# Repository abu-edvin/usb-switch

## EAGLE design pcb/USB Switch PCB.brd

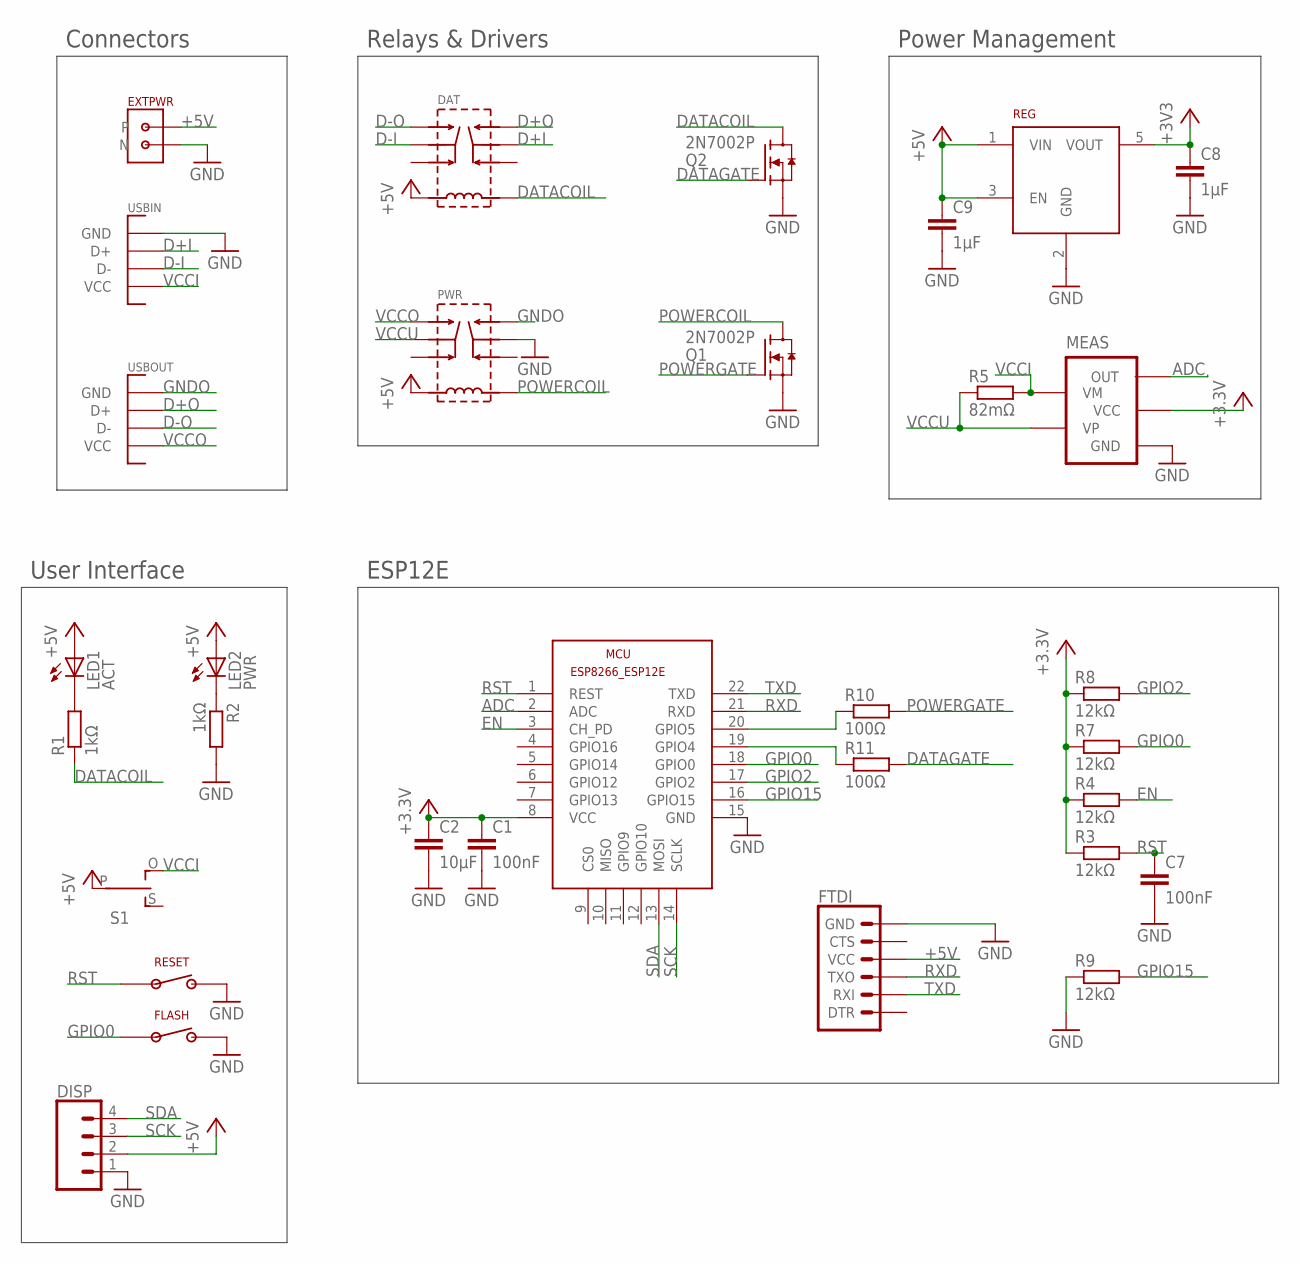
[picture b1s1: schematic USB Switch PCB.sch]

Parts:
C1, C7: 100nF; C0603
C2: 10µF; C0603
C8, C9: 1µF; C0603
DAT: EC2-5NUEC2-5NU; EC2-5NU
DISP: CONN_04; 1X04
EXTPWR: TERMINAL-BLOCK
FLASH: MOMENTARY-SWITCH
FTDI: 6_PIN_SERIAL_TARGET; 1X06
LED1: ACT; CHIPLED_0805
LED2: PWR; CHIPLED_0805
MCU: ESP8266-12EESP8266-ESP12E; ESP8266-ESP12E
MEAS: TCS888; SOT-23-5
PWR: EC2-5NUEC2-5NU; EC2-5NU
Q1, Q2: 2N7002P; SOT23
R1, R2: 1kΩ; R0603
R3, R4, R7, R8, R9: 12kΩ; R0603
R5: 82mΩ; R1206
R10, R11: 100Ω; R0603
REG: MIC5504-3.3YM5SOT23; SOT-23-5
RESET: MOMENTARY-SWITCH
S1: SWITCH
USBIN: USB-B
USBOUT: UE27-USBA

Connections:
+3V3: C8.1, REG.5 (VOUT)
+5V: C1.1, C2.1, C9.1, DAT.1, DISP.2, EXTPWR.P, FTDI.4 (VCC), LED1.A, LED2.A, MCU.8 (VCC), MEAS.5 (VCC), PWR.1, R3.1, R4.1, R7.1, R8.1, REG.1 (VIN), REG.3 (EN), S1.P
ADC: MCU.2 (ADC), MEAS.1 (OUT)
D+I: DAT.9 (C2), USBIN.3 (D+)
D+O: DAT.8 (A2), USBOUT.D+
D-I: DAT.4 (C1), USBIN.2 (D-)
D-O: DAT.5 (A1), USBOUT.D-
DATACOIL: DAT.12 (N), Q2.3 (D), R1.1
DATAGATE: Q2.1 (G), R11.2
EN: MCU.3 (CH_PD), R4.2
GND: C1.2, C2.2, C7.2, C8.2, C9.2, DISP.1, EXTPWR.N, FLASH.P$2, FTDI.6 (GND), MCU.15 (GND), MEAS.2 (GND), PWR.9 (C2), Q1.2 (S), Q2.2 (S), R2.2, R9.1, REG.2 (GND), RESET.P$2, USBIN.4 (GND), USBIN.P$1 (GND), USBIN.P$2 (GND)
GNDO: PWR.8 (A2), USBOUT.GND, USBOUT.P$0 (GND), USBOUT.P$1 (GND)
GPIO0: FLASH.P$1, MCU.18 (GPIO0), R7.2
GPIO2: MCU.17 (GPIO2), R8.2
GPIO15: MCU.16 (GPIO15), R9.2
unnamed: LED1.C, R1.2
unnamed: LED2.C, R2.1
unnamed: MCU.20 (GPIO5), R10.1
unnamed: MCU.19 (GPIO4), R11.1
POWERCOIL: PWR.12 (N), Q1.3 (D)
POWERGATE: Q1.1 (G), R10.2
RST: C7.1, MCU.1 (REST), R3.2, RESET.P$1
RXD: FTDI.3 (TXO), MCU.21 (RXD)
SCK: DISP.3, MCU.14 (SCLK)
SDA: DISP.4, MCU.13 (MOSI)
TXD: FTDI.2 (RXI), MCU.22 (TXD)
VCCI: MEAS.4 (VM), R5.2, S1.O, USBIN.1 (VCC)
VCCO: PWR.5 (A1), USBOUT.VCC
VCCU: MEAS.3 (VP), PWR.4 (C1), R5.1

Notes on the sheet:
Connectors
Relays & Drivers
Power Management
ESP12E
User Interface

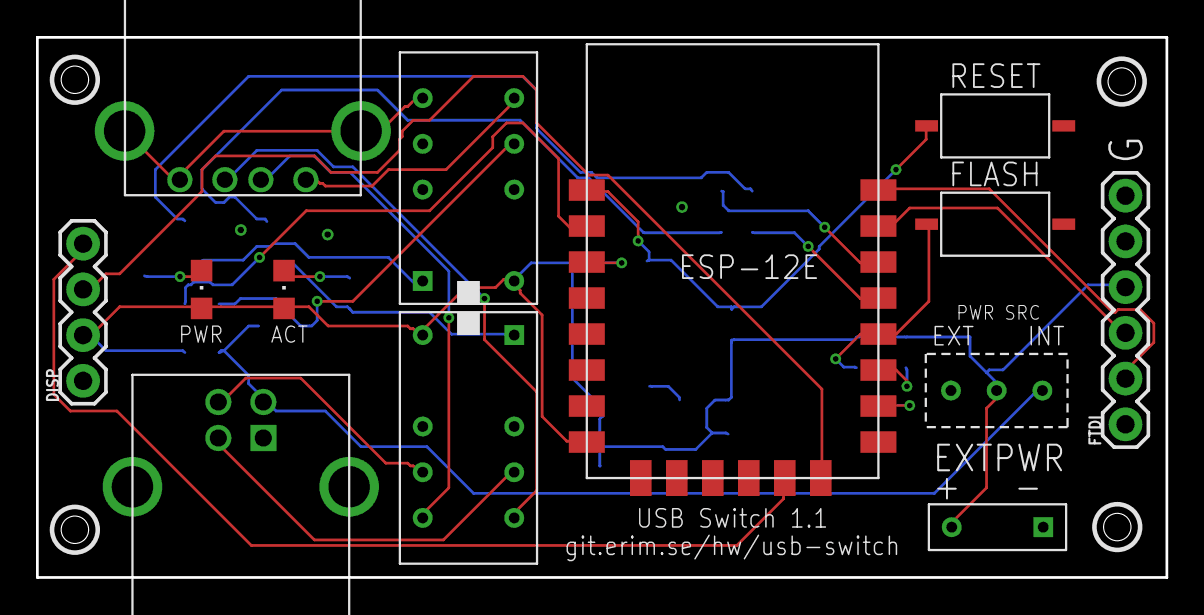
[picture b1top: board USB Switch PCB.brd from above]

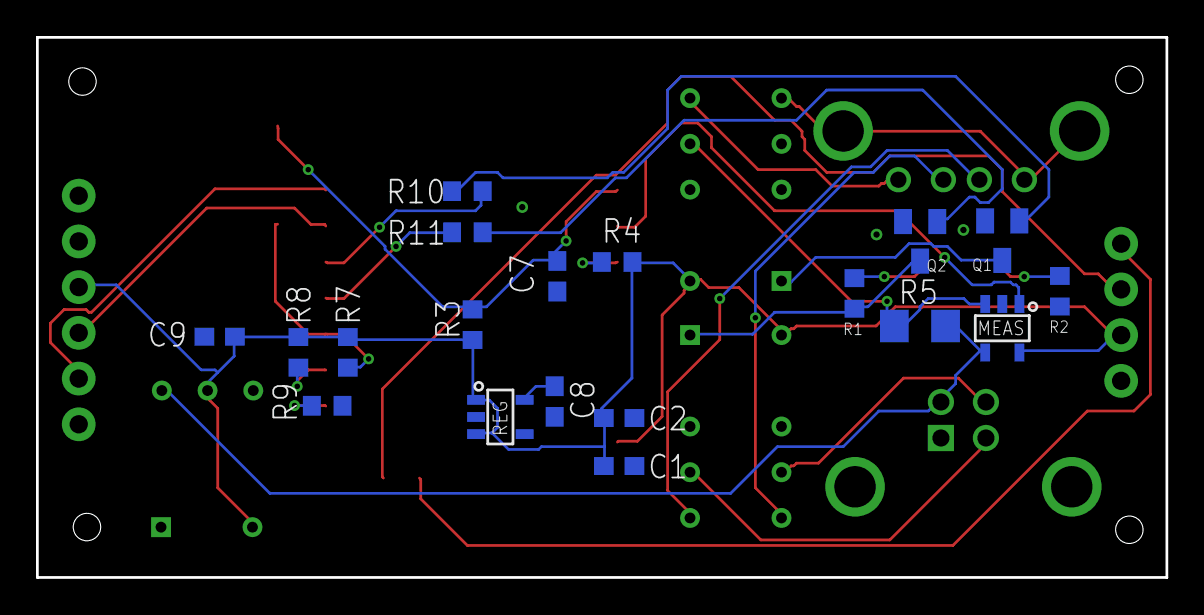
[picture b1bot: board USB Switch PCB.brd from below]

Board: 2 copper layers, 62.8 x 30.0 mm, 32 parts (19 on the bottom side), 29 nets.

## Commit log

2017-06-11 Initial commit.
2017-06-11 Added firmware project.
2017-06-11 Some more PCB work.
2017-06-12 Added micro usb port.
2017-06-13 feat(usb-b): VCC supply fixed.
2017-06-15 More work!
2017-06-16 Yay, board!
2017-06-16 Auto-routed PCB with lots of nice stuff.
2017-06-19 Work work
2017-06-26 More work on switch.
2017-06-26 Final touches.
2017-07-19 I'm gonna start messing shit up soon.
2017-07-24 Working on new board revision.
2017-07-27 More work, looks like shit now.
2017-07-28 Total redesign of, well, everything.
2017-08-09 Starting to look good.
2017-09-24 Converting everything
2017-10-14 Aded momentary switch from banggood.
2017-10-15 Current measurement circuit now done.
2017-10-15 Remade PCB layout.
2017-10-17 Is this final? It sure feels like final!

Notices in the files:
parts and their libraries:
SparkFun-Connectors: Licensing: Creative Commons ShareAlike 4.0 International - https://creativecommons.org/licenses/by-sa/4.0
